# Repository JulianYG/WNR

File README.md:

# WNR
Wireless Neural Recorder

About 10% of the world’s population suffers from epilepsy, a brain function disorder that causes neurons in patients’ brain to fire at an abnormal rate with unregulated patterns. Diagnosis of this condition often involves a medical procedure called electroencephalogram (EEG), which detects the electric pulses created by the neurons.

For most patients, it usually suffices to use scalp EEG to confirm diagnosis. Scalp EEG, also known as Extracranial EEG, uses non-invasive electrodes which are stuck to the surface of the patient’s scalp to detect brain wave signal. For these patients, which account for 70% of the total epilepsy patients, their illness can be controlled through therapy and drugs. However, for the rest 30% of epilepsy patients, the drugs do not work and surgical procedures must be done to remove certain problem sections of the brain to control the epilepsies. If a patient with epilepsy is being considered for epilepsy surgery, it is often necessary to localize the source of the epileptic brain activity with a resolution greater than what is provided by scalp EEG.

Scalp EEG does not provide the resolution of brain activity data required for neurosurgeons to operate on as the cerebrospinal fluid, skull and scalp smear the electrical potentials from the scalp electrodes. To perform the epilepsy surgery, neurosurgeons typically first implant grid of electrodes or penetrating depth electrodes under the dura (brain) mater, through either a craniotomy or a burr hole. The recording of these signals is referred to as electrocorticography (ECoG), subdural EEG (sdEEG) or intracranial EEG (icEEG)--all terms for the same thing. The signal recorded from the intracranial EEG is on a different scale of activity than the brain activity recorded from scalp EEG. Because signals are collected by directly contact with electrodes, Low voltage, high frequency components that cannot be seen easily or at all in scalp EEG can be seen clearly in EEG.
 
The current method of collecting intracranial EEG data from a patient’s brain is through a tethered cord to a monitoring and recording device on premise at a clinic or hospital. The intracranial EEG records the spontaneous electrical activity of the brain measuring voltage fluctuations resulting from ionic current within the neurons of the brain as recorded from multiple electrodes. This tethered EEG procedure is high invasive and disruptive to patients’ lives as they are confined to a hospital bed for several days to a week while doctors wait for very small windows of epileptic episodes to occur to gather a limited amount of useful information.
 
Wireless Neural Recorder’s (WNR) objective is to create a wireless monitoring solution to the problem of neural recording, allowing users the freedom and mobility to return to their normal lives at home while also enabling doctors to obtain sufficient neural data required to treat their patients’ conditions effectively.
 
The figure above provides an illustration about the position of the final device in relation to the brain after it is implanted.  Before we look into our proposed system for a wireless neural recording device, we will provide an overview of the components of the more common wired equivalent.  The general system diagram flow of wired neural recording machines is shown below.

Data from the electrodes (fig. 4a) is digitized by the analog front end (fig. 4b) and can be sent directly to the server (fig. 4c).  Generally, the server will be running continuously from a inexhaustive power supply, and thus, will not have any power constraints.  Since transmission is not through an intermediary medium, like air or water, that separates the where the data obtained and where the data needs to be transmitted, the data can be sent directly to the server for storage and analysis, without any need for preprocessing or any additional overhead.

However since the goal of our design is to provide a wireless solution to neural recording and data storage, our system design becomes more complicated.

The figure above shows the proposed design of our entire system.  The front-end remains relatively the same.  Electrode data is sampled by the analog front-end, which accounts for low-noise signal amplification and DC offset rejection that arises from the nature of brain signals and the electric potential difference that forms at the contact point between the electrode and the brain[3].  Once the data is digitized, it is passed into a CPU or microprocessor (fig. 5c) where the data is preprocessed for transmission.  When the data has been processed for transmission, it is passed to the wireless transmitter (fig. 5d) and transmitted across the air medium (fig. 5e) to a server (fig. 5f), which can be a module near or on the patient’s body.  In the server, the data can be stored, viewed, and analyzed for deviations from standard brain activities.  It was specified by Dr. Nitin Tandon, our sponsor from UTHealth, that the device should ideally fit within a 5 x 5 x 10 mm container (maximum dimensions was specified to be 8 x 8 x 10 mm), which is an extremely aggressive size constraint and limiting factor.

Raw pulses observed from electrodes are generally in the microvolt range and require amplification to be accurately digitized[4].  Multiple problems arise because of this.  Before sending the signal to be digitized in the analog to digital converter (ADC), we must send the signal through a circuit that amplifies the signal, while keeping a good signal-to-noise-ratio[4].  Proposed solutions exist in academia and in the market[3][4][5][6], so it is a matter of choosing the implementation that best suits our system’s needs.  Additionally, when electrodes come in contact with the brain, an electric potential difference or DC offset is created that can be as great as a few volts[4].  Recording the signal without removing the DC offset will generally yield poor results because the DC offset is orders of magnitudes greater than the actual brain pulse[3].  Therefore, the analog circuit we create for the front end of our system must also reject as much DC offset as possible.

Beginning from the microprocessor preprocessing section of the system block diagram (fig. 5c), there are deviations from the wired neural recorder system (fig. 4).  At this stage, the data will be processed based on the precision of the sampled data points as well as the limitations of the wireless transmission protocol we decide to use.  For instance, one viable transmission protocol that we are considering is Bluetooth Low Energy.  Bluetooth Low energy has a maximum data transfer rate of 260 kb/s[7].  If we decide to sample each contact point with a precision of eight bits, then the channel can support a data point transfer rate of 32,500 data points per second.  This means if we have more than 32 channels or contact points sampled at 1 kHz, all collecting and transferring data to the same server, then the channel capacity for bluetooth low energy will be incapable of supporting the entire offered load from the electrodes, and the system will incur data loss.  Then in order for the transmission rate to keep up with the sampling rate from all nodes in the array, the data coming in for transmission has to be downsampled or compressed in some other way in order to reduce the amount of bits transmitted across the channel.

Given our system design requirements, we have identified three main challenges that we will face in designing our device: wireless data transmission, power, and safety regulations. Our wireless data transmission protocol must be power efficient while having enough bandwidth and transmission speed to send 128kb/s. Five potential wireless options were considered but we decided to go with Bluetooth Low Energy as it provides adequate communication security and power efficiency[8]. It has high range, medium bandwidth and medium data transfer rate but high power efficiency. It is the best tradeoff in terms of performance to power, while also being secured via encryption and other privacy protocols. Power is another major concern as we will be sampling and sending data very frequently at the detriment of our battery life. Given our small form factor, the batteries for our application will be limited in size, hence batteries need to be high density, high efficiency batteries similar to ones found in pacemakers.  Each electrode and wireless control unit should have the capability of sampling and transmitting data for at least 24 hours.  However, there are very few batteries that fit within the size of 5 x 5 x 10 or 8 x 8 x 10 mm that provides significant amounts of power, so the battery will be one of the major limiting factors of the project.  If power consumption goes above what the batteries can provide, then a method for reducing the system’s power, most likely by decreasing the rate at which data is transmitted to the receiver, must be implemented. Lastly our device has to conform to multiple standards and guidelines set by the FCC, FDA, and HIPPA. Our medical device has a communications link, so it not only has to conform to extensive safety testing perform by the Food and Drug Administration (FDA)[9] but also compatibility testing by the Federal Communication Commission (FCC)[10]. We are working with patient data so we also have to ensure that we are HIPPA compliant and securing our data with no unauthorized access outside of patients and approved medical professionals[11].
 
In order to best prepare ourselves for marketing our product to professional health-care providers, research has been done on the procedure with which hospitals purchase medical devices. Hospitals generally have a well established pipeline for acquiring new equipments[13]. First, hospitals’ directors undergo a strategic planning phase during which the they decide which type of medical devices that the hospital needs. After strategic planning, a rigorous assessment procedure is performed on multiple competing existing technologies with cost-benefit assessments. After the technology has been assessed and the final decision of purchase has been made, the technology acquisition phase of the purchasing process is engaged and final contracts are signed with medical device manufacturers.

With the knowledge of how our customers will assess our products, we look at our competitors against whom our product will compete for the final contract. For our wireless neural recorder, we found that are very few existing commercial EEGs rated for wireless human brain wave test data recording and monitoring. This is because prevalent EEG technology is generally wired and limiting in terms of the freedom and dignity of epilepsy patients, and wireless intracranial EEG recording is a very new field with very few competitors. We identified our two main competitors to be DEUTRON and NEUROPACE, but both their technologies have limitations that make their options less than ideal. We will discuss our competitors’ options more in depth in our market analysis sections.

WNR envisions a future where epilepsy patients no longer have to spend days painfully confined to a hospital bed just so a EEG electrodes can gather data to send to a computer; but, rather a future where patients can go about their daily lives at home while an implanted EEG wirelessly sends data to a mobile recording device in real time both efficiently and securely using state-of-the-art technologies allowing for more extensive real world epileptic data collection.

REFERENCES

[1]   "Method of the Month: EEG." Brain In A Vat. 4 Sept. 2007. Web. 25 Sept. 2015. 
[2]   한양대학교 Jang’s Lab." 한양대학교 Jang’s Lab. Web. 25 Sept. 2015.
[3]   Bharucha, Eric, Hassan Sepehrian, and Benoit Gosselin. "A Survey of Neural Front       End Amplifiers and Their Requirements toward Practical Neural Interfaces." Journal of Low Power Electronics and Applications JLPEA (2014): 268-91. Print.
[4]   Harrison, R.r., and C. Charles. "A Low-power Low-noise Cmos for Amplifier Neural Recording Applications." IEEE J. Solid-State Circuits IEEE Journal of Solid-State Circuits: 958-65. Print.
[5]   Harrison, Reid R. "Wireless Neural Recording With Single Low-Power Integrated Circuit." IEEE TRANSACTIONS ON NEURAL SYSTEMS AND REHABILITATION ENGINEERING 17.4 (2009): 322-29. Print.
[6]   Harrison, R.r. "The Design of Integrated Circuits to Observe Brain Activity." Proceedings of the IEEE Proc. IEEE: 1203-216. Print.
[7]   "Bluetooth 4.2 Core Specifications Finalized." RSS. Web. 25 Sept. 2015.
[8]   Smith, P. (2011, August 8). Comparing Low-Power Wireless Technologies. Retrieved September 25, 2015. 
[9]   Guidance Documents (Medical Devices and Radiation-Emitting Products). (n.d.). Retrieved September 25, 2015. 
[10] Radio Frequency Wireless Technology in Medical Devices - Guidance for Industry and Food and Drug Administration Staff. (n.d.). Retrieved September 25, 2015. 
[11] HHS.gov. (n.d.). Retrieved September 25, 2015. 
[12] Alpert, Alec. "Understanding How Hospitals Buy Medical Technology." 2009. Web. 25 Sept. 2015.
[13] "Fast Facts on US Hospitals." Fast Facts on US Hospitals. Web. 25 Sept. 2015.

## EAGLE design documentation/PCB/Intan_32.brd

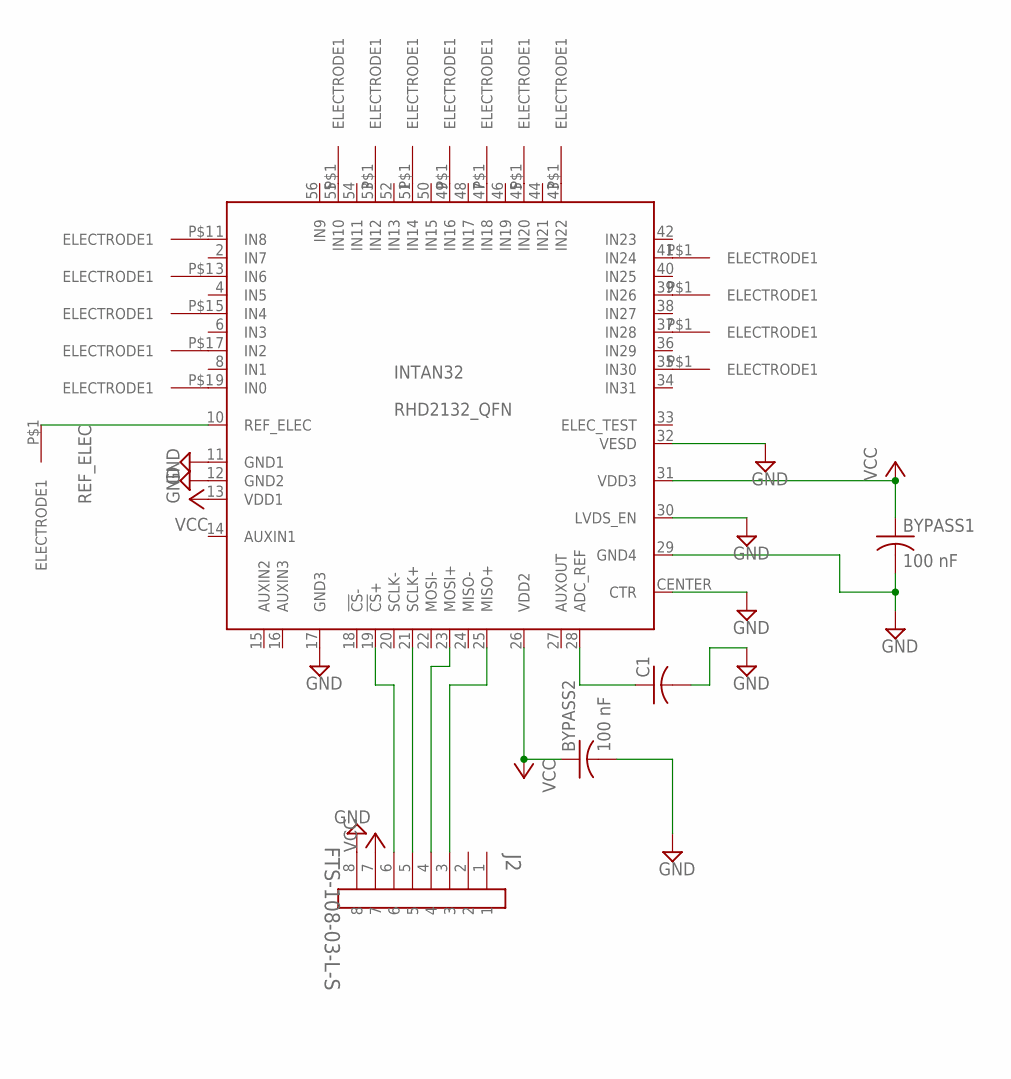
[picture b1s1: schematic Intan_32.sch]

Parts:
BYPASS1, BYPASS2: 100 nF; C0402
C1: C-USC0402; C0402
INTAN32: RHD2132_QFN; QFN56_8_X_8_LARGE
J2: FTS-108-03-L-S; SAMTEC_FTS-108-03-S
REF_ELEC: INTAN_ELECTRODE_HOLE_2323MIL; INTAN_ELECTRODE_HOLE_23
U$1, U$2, U$3, U$4, U$5, U$6, U$7, U$8, U$9, U$10, U$11, U$12, U$13, U$14, U$15, U$16: INTAN_ELECTRODE_HOLE_2323MIL; INTAN_ELECTRODE_HOLE_23

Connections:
GND: BYPASS1.2, BYPASS2.2, C1.2, INTAN32.11 (GND1), INTAN32.12 (GND2), INTAN32.17 (GND3), INTAN32.29 (GND4), INTAN32.30 (LVDS_EN), INTAN32.32 (VESD), INTAN32.CENTER (CTR), J2.8
unnamed: INTAN32.25 (MISO+), J2.3
unnamed: C1.1, INTAN32.28 (ADC_REF)
unnamed: INTAN32.9 (IN0), U$1.P$1
unnamed: INTAN32.7 (IN2), U$2.P$1
unnamed: INTAN32.23 (MOSI+), J2.4
unnamed: INTAN32.5 (IN4), U$3.P$1
unnamed: INTAN32.3 (IN6), U$4.P$1
unnamed: INTAN32.1 (IN8), U$5.P$1
unnamed: INTAN32.55 (IN10), U$6.P$1
unnamed: INTAN32.19 (!CS!+), J2.6
unnamed: INTAN32.21 (SCLK+), J2.5
unnamed: INTAN32.53 (IN12), U$7.P$1
unnamed: INTAN32.51 (IN14), U$8.P$1
unnamed: INTAN32.49 (IN16), U$9.P$1
unnamed: INTAN32.47 (IN18), U$10.P$1
unnamed: INTAN32.45 (IN20), U$11.P$1
unnamed: INTAN32.43 (IN22), U$12.P$1
unnamed: INTAN32.41 (IN24), U$13.P$1
unnamed: INTAN32.39 (IN26), U$14.P$1
unnamed: INTAN32.37 (IN28), U$15.P$1
unnamed: INTAN32.35 (IN30), U$16.P$1
REF_ELEC: INTAN32.10 (REF_ELEC), REF_ELEC.P$1
VCC: BYPASS1.1, BYPASS2.1, INTAN32.13 (VDD1), INTAN32.26 (VDD2), INTAN32.31 (VDD3), J2.7

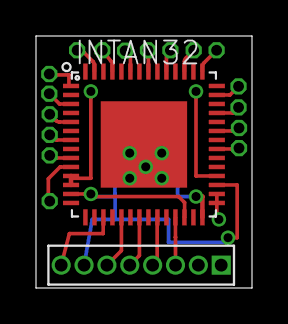
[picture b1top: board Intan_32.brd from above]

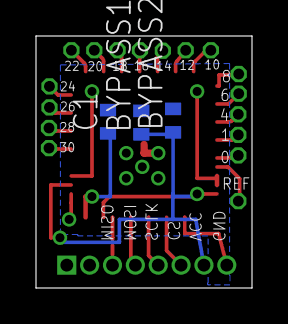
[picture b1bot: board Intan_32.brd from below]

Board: 2 copper layers, 12.0 x 14.0 mm, 22 parts (3 on the bottom side), 24 nets.

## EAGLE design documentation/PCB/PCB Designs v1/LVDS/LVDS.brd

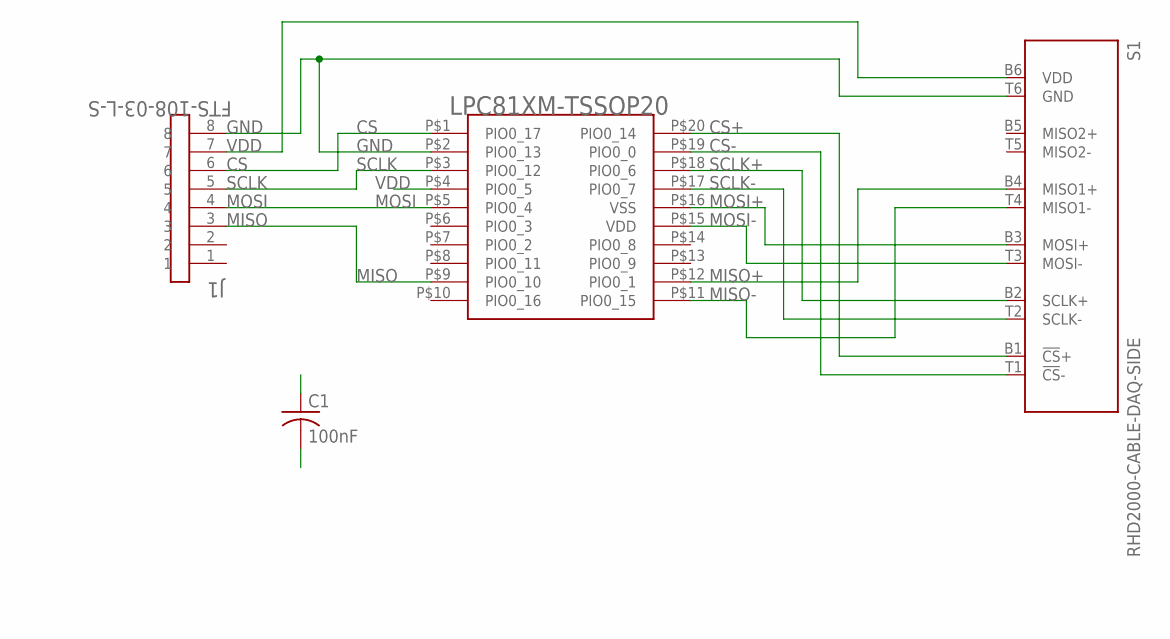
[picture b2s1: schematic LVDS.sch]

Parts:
C1: 100nF; C0402
J1: FTS-108-03-L-S; SAMTEC_FTS-108-03-S
LVDS: LPC81XM_TSSOP20; TSSOP20
S1: RHD2000-CABLE-DAQ-SIDE; OMNETICS_PZN-12-AA

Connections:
CS: J1.6, LVDS.P$1 (PIO0_17)
CS+: LVDS.P$20 (PIO0_14), S1.B1 (!CS!+)
CS-: LVDS.P$19 (PIO0_0), S1.T1 (!CS!-)
GND: C1.2, J1.8, LVDS.P$2 (PIO0_13), S1.T6 (GND)
MISO: J1.3, LVDS.P$9 (PIO0_10)
MISO+: LVDS.P$12 (PIO0_1), S1.B4 (MISO1+)
MISO-: LVDS.P$11 (PIO0_15), S1.T4 (MISO1-)
MOSI: J1.4, LVDS.P$5 (PIO0_4)
MOSI+: LVDS.P$16 (VSS), S1.B3 (MOSI+)
MOSI-: LVDS.P$15 (VDD), S1.T3 (MOSI-)
SCLK: J1.5, LVDS.P$3 (PIO0_12)
SCLK+: LVDS.P$18 (PIO0_6), S1.B2 (SCLK+)
SCLK-: LVDS.P$17 (PIO0_7), S1.T2 (SCLK-)
VDD: C1.1, J1.7, LVDS.P$4 (PIO0_5), S1.B6 (VDD)

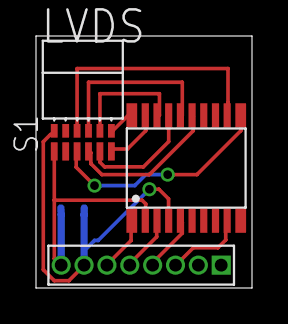
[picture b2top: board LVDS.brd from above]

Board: 2 copper layers, 12.0 x 14.0 mm, 4 parts (1 on the bottom side), 14 nets.

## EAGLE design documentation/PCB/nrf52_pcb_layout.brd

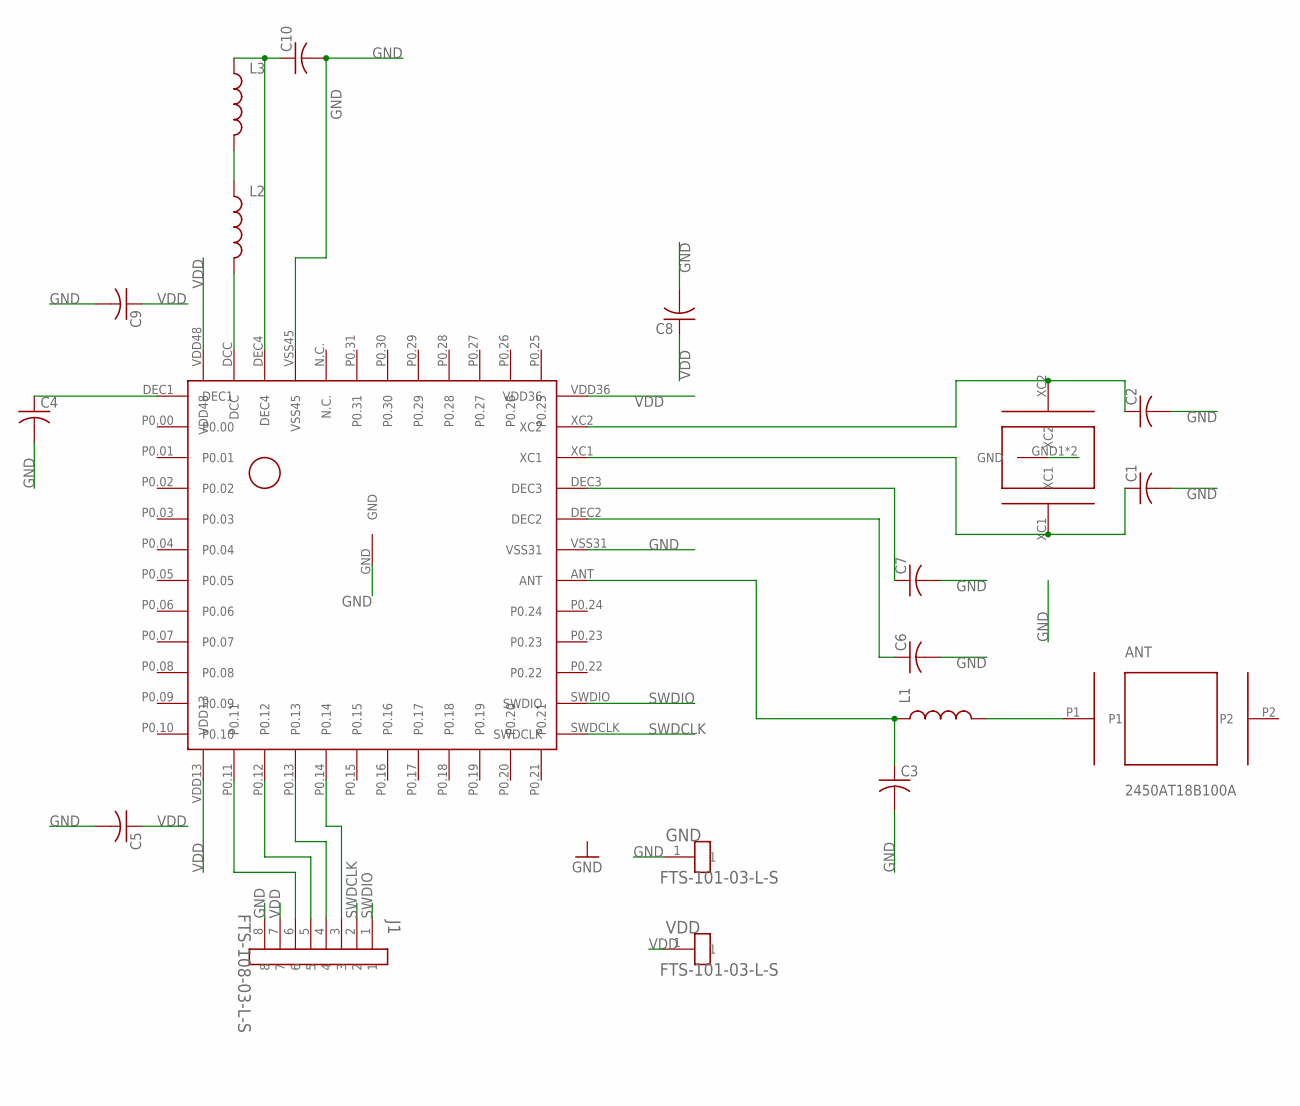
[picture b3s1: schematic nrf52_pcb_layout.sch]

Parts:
ANT: 2450AT18B100A; 2450AT18B100
C1, C2, C3, C4, C5, C6, C7, C8: C-USC0402; C0402
C9, C10: C-USC0603; C0603
GND: FTS-101-03-L-S; SAMTEC_FTS-101-03-S
J1: FTS-108-03-L-S; SAMTEC_FTS-108-03-S
L1, L3: INDUCTOR0402; C0402
L2: INDUCTOR0603; 0603
NRF52: NRF52832-QFN48
VDD: FTS-101-03-L-S; SAMTEC_FTS-101-03-S
X1: XTAL-SMD-2016SMD-2016; XTAL-SMD-2016

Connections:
GND: C1.2, C2.2, C3.2, C4.2, C5.2, C6.2, C7.2, C8.2, C9.2, C10.2, GND.1, J1.8, NRF52.GND, NRF52.VSS31, NRF52.VSS45, X1.GND1 (GND), X1.GND2 (GND)
unnamed: ANT.P1, L1.2
unnamed: L2.1, L3.2
unnamed: C4.1, NRF52.DEC1
unnamed: L2.2, NRF52.DCC
unnamed: C10.1, L3.1, NRF52.DEC4
unnamed: C2.1, NRF52.XC2, X1.XC2
unnamed: C1.1, NRF52.XC1, X1.XC1
unnamed: J1.6, NRF52.P0.11
unnamed: J1.5, NRF52.P0.12
unnamed: J1.4, NRF52.P0.13
unnamed: J1.3, NRF52.P0.14
unnamed: C3.1, L1.1, NRF52.ANT
unnamed: C7.1, NRF52.DEC3
unnamed: C6.1, NRF52.DEC2
SWDCLK: J1.2, NRF52.SWDCLK
SWDIO: J1.1, NRF52.SWDIO
VDD: C5.1, C8.1, C9.1, J1.7, NRF52.VDD13, NRF52.VDD36, NRF52.VDD48, VDD.1

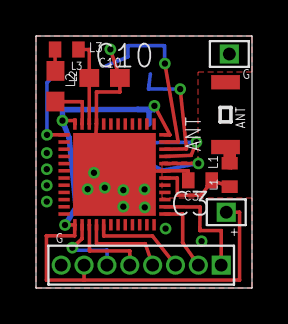
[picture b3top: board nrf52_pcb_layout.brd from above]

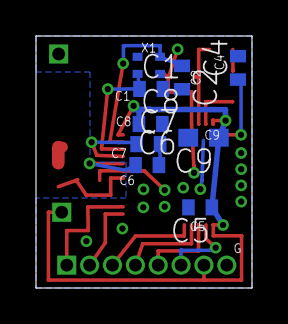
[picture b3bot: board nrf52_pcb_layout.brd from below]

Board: 2 copper layers, 12.0 x 14.0 mm, 19 parts (9 on the bottom side), 18 nets.

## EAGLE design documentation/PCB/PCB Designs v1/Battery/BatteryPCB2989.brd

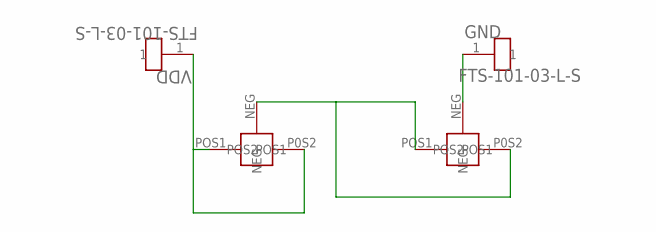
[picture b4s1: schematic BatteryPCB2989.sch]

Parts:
GND: FTS-101-03-L-S; SAMTEC_FTS-101-03-S
U$1, U$2: 2989NOHOLE
VDD: FTS-101-03-L-S; SAMTEC_FTS-101-03-S

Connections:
unnamed: U$1.NEG, U$2.P0S2 (POS2), U$2.POS1
unnamed: GND.1, U$2.NEG
unnamed: U$1.P0S2 (POS2), U$1.POS1, VDD.1

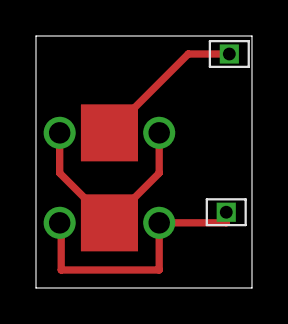
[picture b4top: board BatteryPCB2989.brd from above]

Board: 2 copper layers, 12.0 x 14.0 mm, 4 parts (0 on the bottom side), 3 nets.

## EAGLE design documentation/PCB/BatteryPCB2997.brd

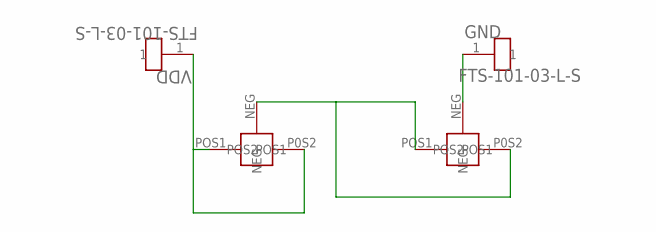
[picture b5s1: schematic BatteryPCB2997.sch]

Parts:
GND: FTS-101-03-L-S; SAMTEC_FTS-101-03-S
U$3, U$4: 2997
VDD: FTS-101-03-L-S; SAMTEC_FTS-101-03-S

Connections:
unnamed: U$3.NEG, U$4.P0S2 (POS2), U$4.POS1
unnamed: GND.1, U$4.NEG
unnamed: U$3.P0S2 (POS2), U$3.POS1, VDD.1

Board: 2 copper layers, 4 parts (1 on the bottom side), 3 nets, no tracks yet.

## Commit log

2016-01-20 Initial commit for UART compression
    Make sure copy all files in uart folder to the lib folder under
    components/libraries/uart
2016-01-22 verified compressibility
2016-01-22 argv1
2016-01-23 Add modified BLE uart example.
2016-01-27 for ble compression
2016-02-03 test
2016-02-03 changed
2016-02-03 fixed errors
2016-02-03 new try
2016-02-03 correct...
2016-02-03 minor fixes
2016-02-03 one more glitch
2016-02-11 Add nrf52 sdk with throughput test ported from nrf51 example code.
2016-02-15 Add the nRF52 throughput test project that was missing in the previous commit.
2016-02-15 my SDK
2016-02-18 fifo new
2016-02-18 modified
2016-02-24 heatshrink
2016-02-25 see how much
2016-02-25 heat shrink
2016-02-26 should work
2016-02-26 back
2016-03-08 Add Intan SPI code
2016-03-12 Add SPI + Compression sdk
2016-03-16 half
2016-03-17 comp
2016-03-17 compiles w/o
2016-03-22 good starting point
2016-03-22 bad ending point
2016-03-24 abak
2016-04-03 merged esb 51 and 52
2016-04-04 send data first try
2016-04-06 with receiver and not working C
2016-04-06 fragile
2016-04-07 another C try
2016-04-07 littleb it more
2016-04-11 right receiver.py
2016-04-12 decoder
2016-04-12 receiver on windows w/ C lib to read serial port and decompress
2016-04-12 working partly
2016-04-12 more working
2016-04-13 working before plot
2016-04-13 writign to csv
2016-04-13 working uart decomp
2016-04-13 should be workign BLE decomp
2016-04-13 only needs test
2016-04-14 workign ble
2016-04-14 Add full system sdk
2016-04-14 purged repo
2016-04-14 clean up
2016-04-14 data
2016-04-14 multi
2016-04-14 multilink work
2016-04-14 working demo
2016-04-27 final report
2016-05-17 Add demo testing code and documentation from Google Drive accumulated from the 2015 - 2016 academic school year.

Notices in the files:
parts and their libraries:
SparkFun: Licensing: CC v3.0 Share-Alike You are welcome to use this library for commercial purposes.
